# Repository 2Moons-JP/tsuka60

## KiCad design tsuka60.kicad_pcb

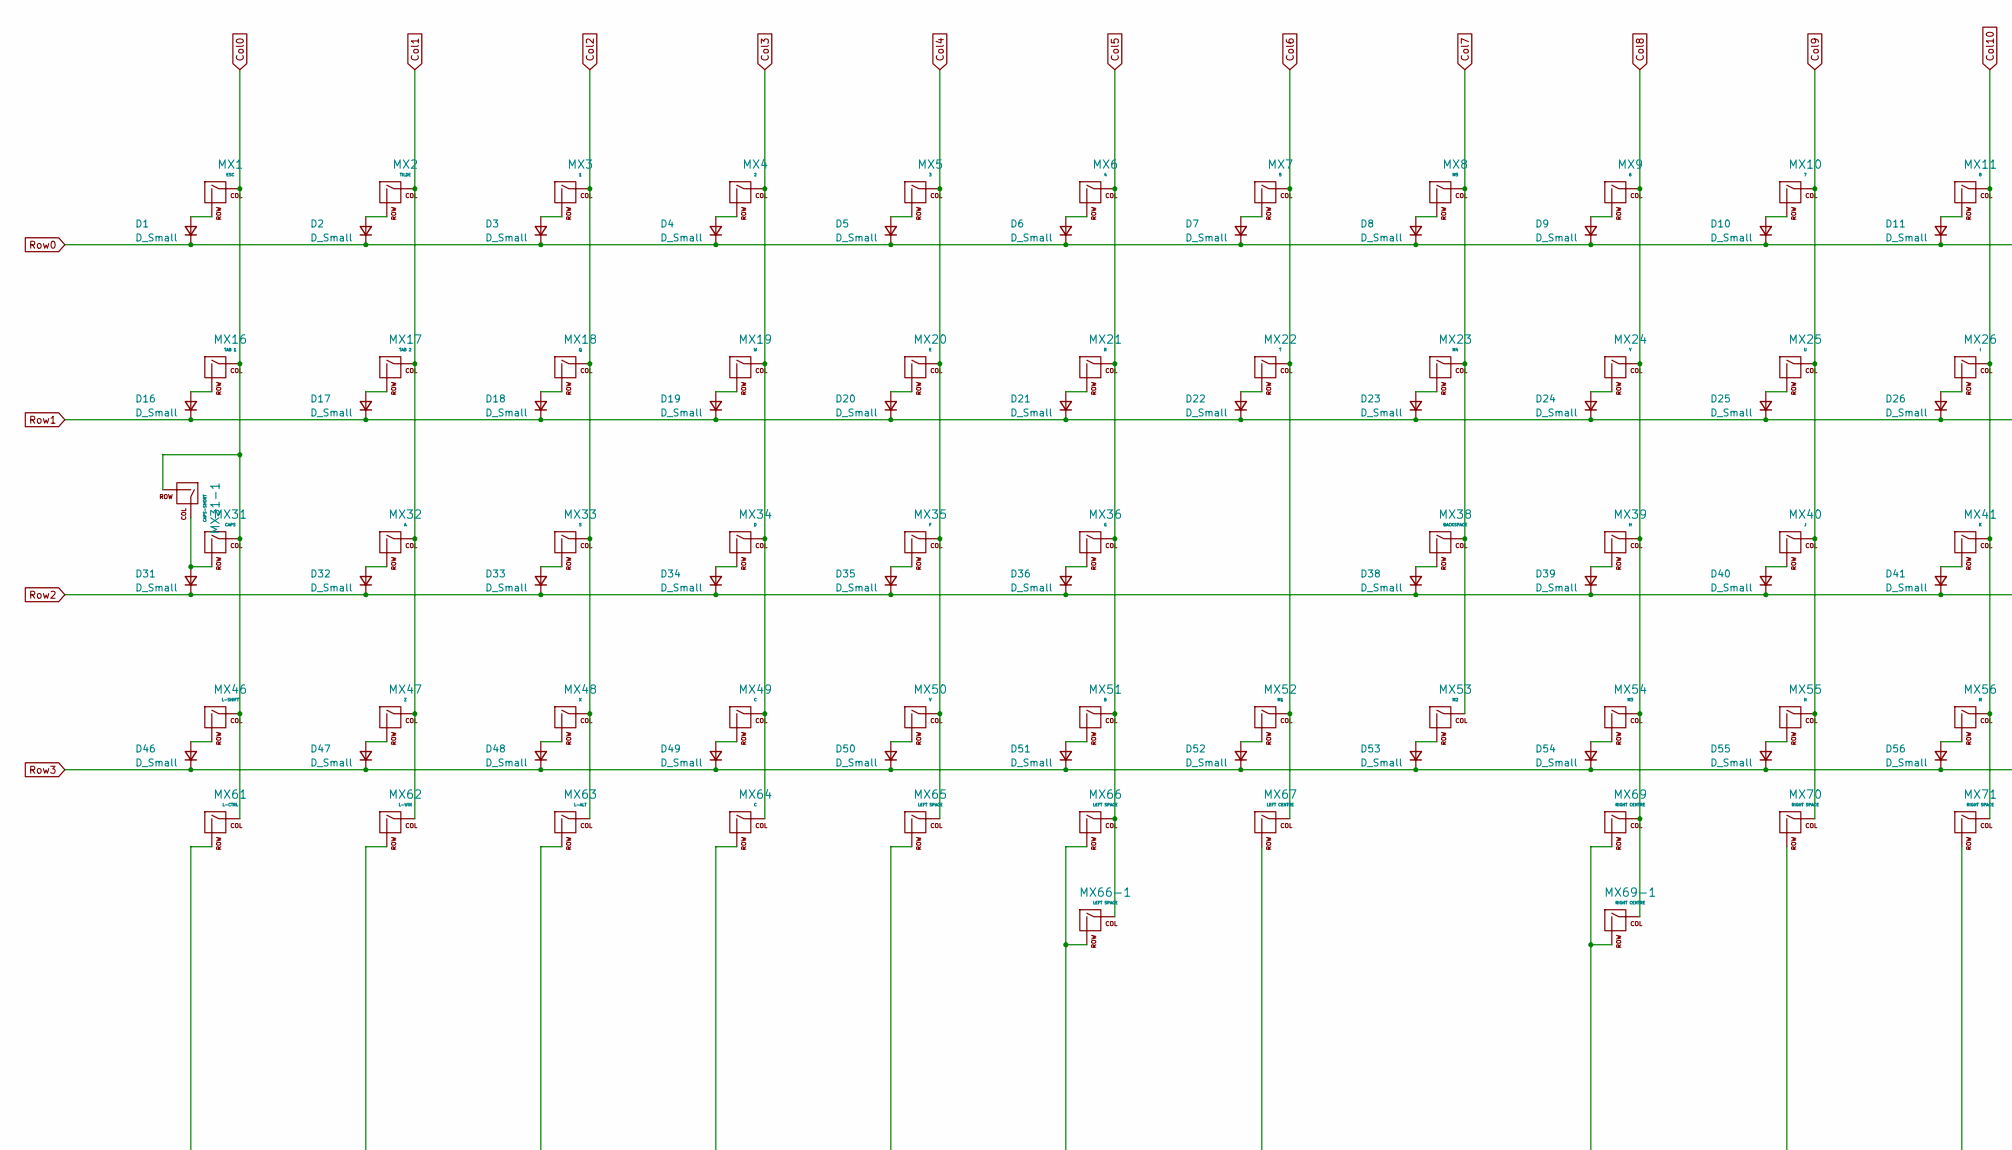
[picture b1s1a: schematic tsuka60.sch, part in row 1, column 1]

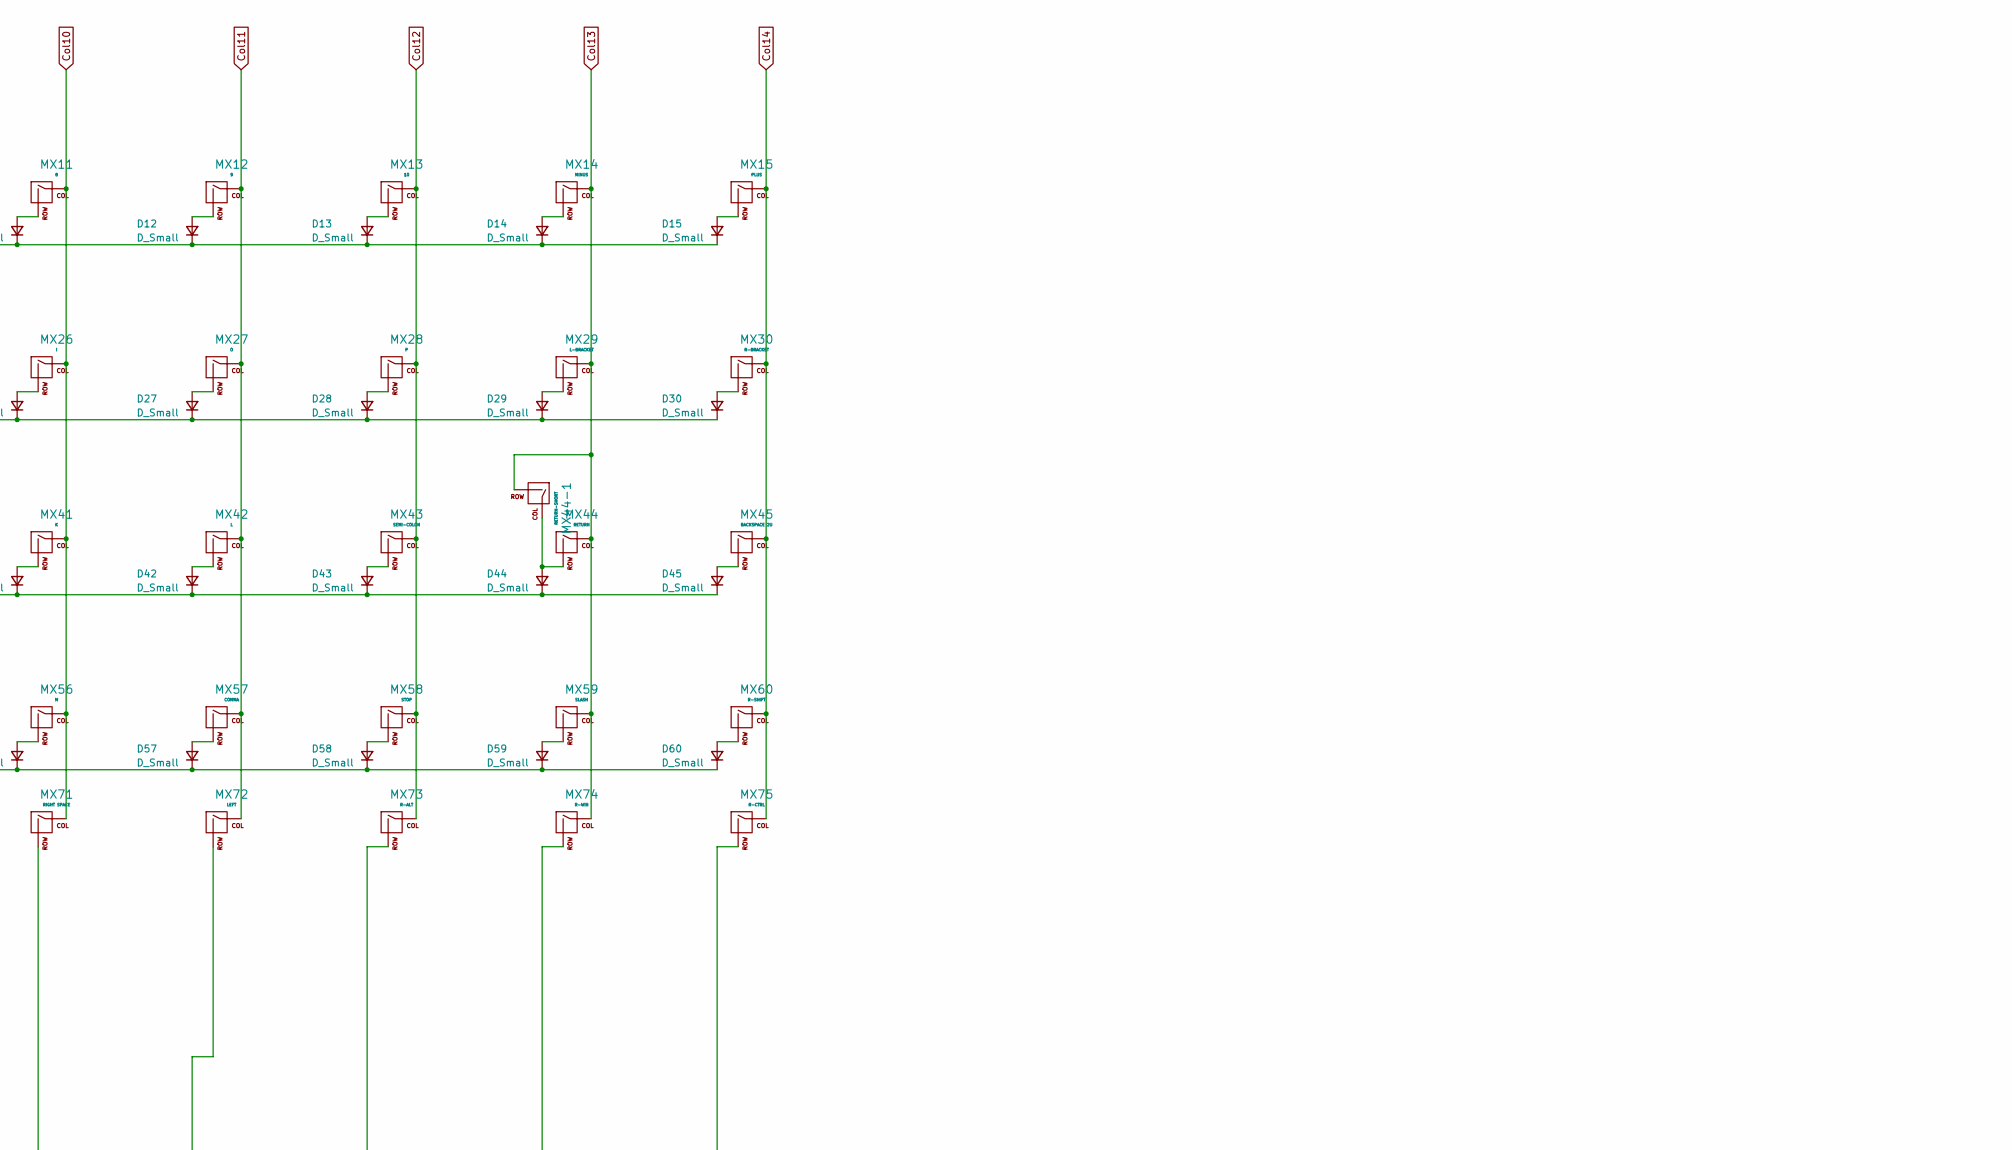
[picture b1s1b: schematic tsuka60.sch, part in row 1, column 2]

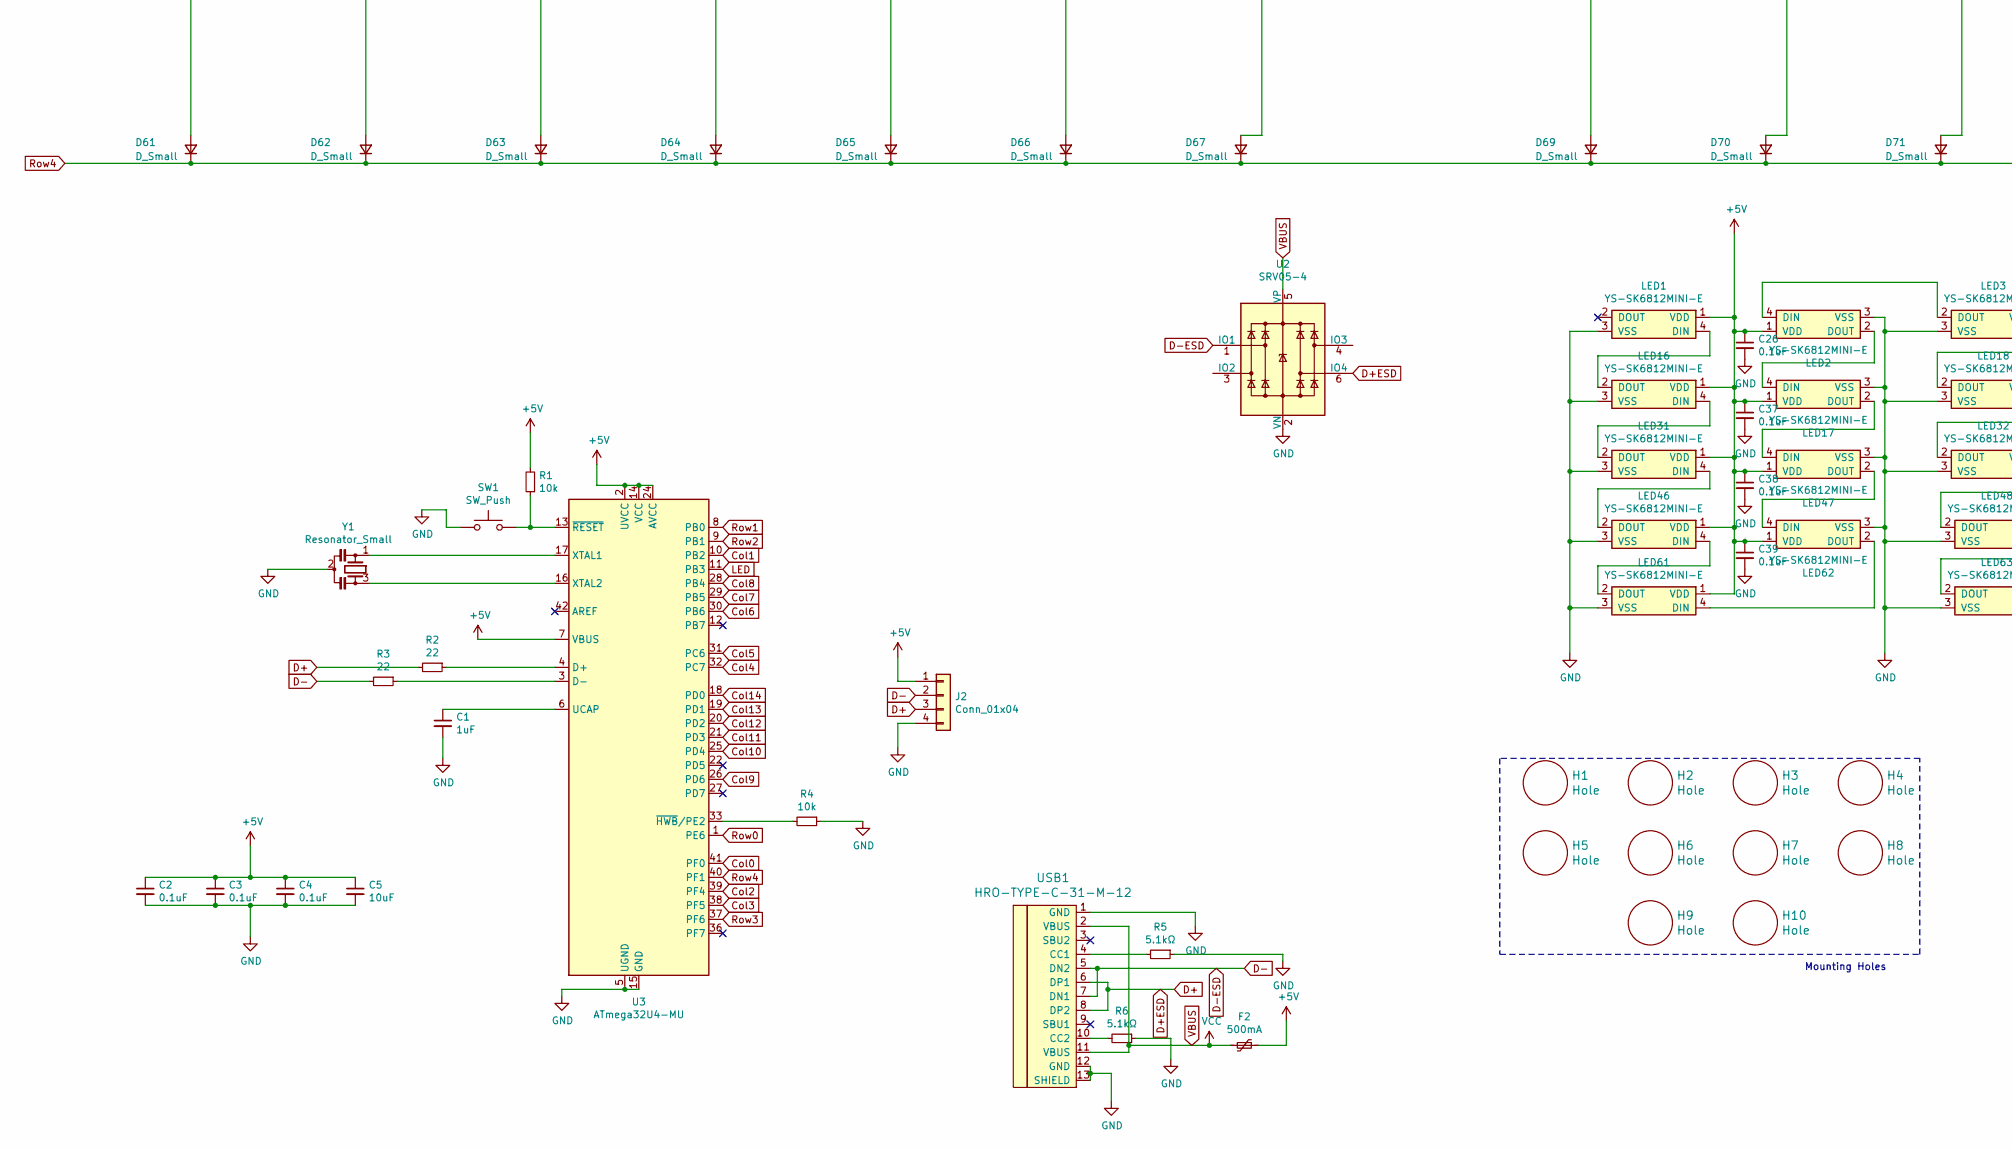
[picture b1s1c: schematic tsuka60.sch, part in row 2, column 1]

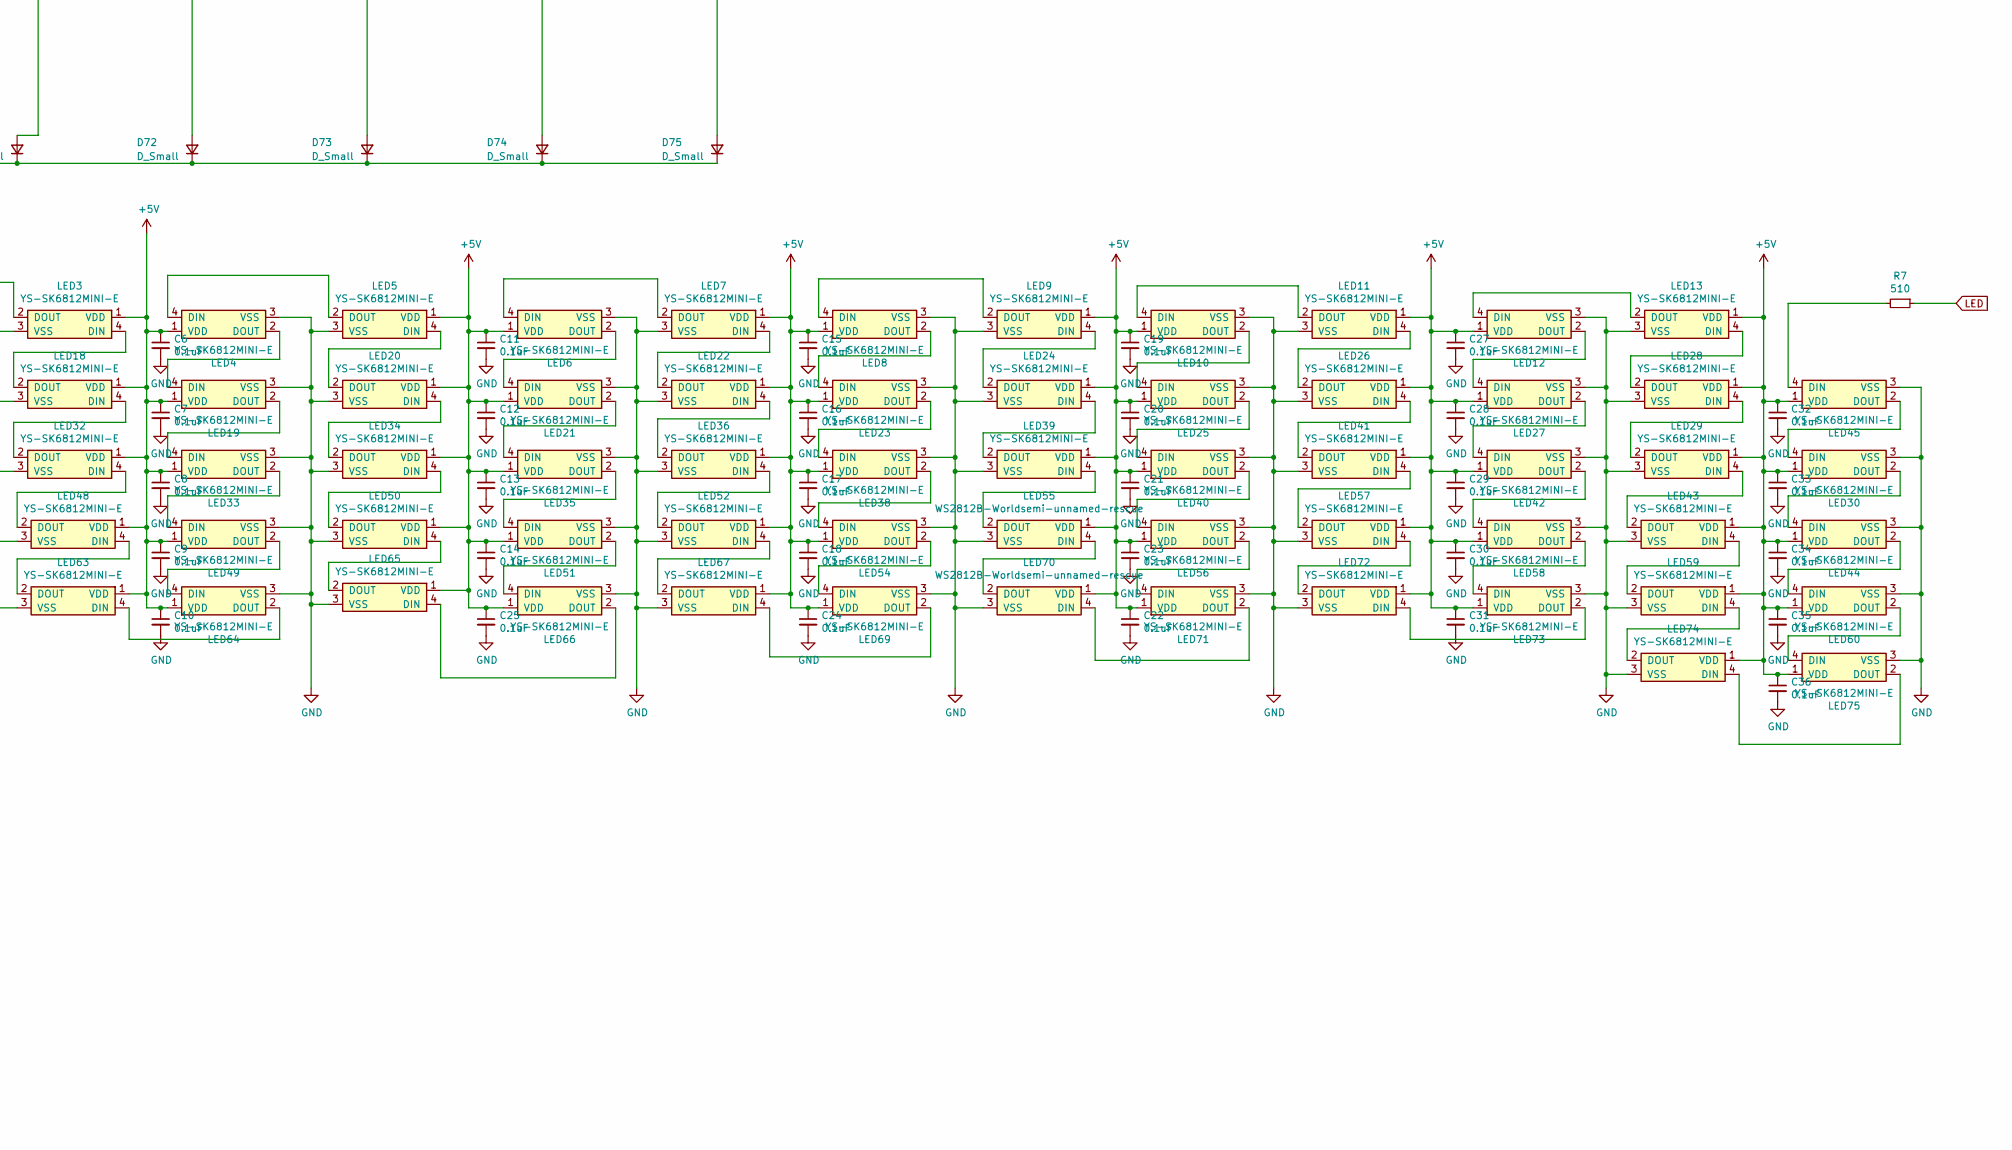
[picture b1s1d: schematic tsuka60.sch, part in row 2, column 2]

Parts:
C1: 1uF; C_0805_2012Metric
C2, C3, C4, C6, C7, C8, C9, C10, C11, C12, C13, C14, C15, C16, C17, C18, C19, C20, C21, C22, C23, C24, C25, C26, C27, C28, C29, C30, C31, C32, C33, C34, C35, C36, C37, C38, C39: 0.1uF; C_0805_2012Metric
C5: 10uF; C_0805_2012Metric
D1, D2, D3, D4, D5, D6, D7, D8, D9, D10, D11, D12, D13, D14, D15, D16, D17, D18, D19, D20, D21, D22, D23, D24, D25, D26, D27, D28, D29, D30, D31, D32, D33, D34, D35, D36, D38, D39, D40, D41, D42, D43, D44, D45, D46, D47, D48, D49, D50, D51, D52, D53, D54, D55, D56, D57, D58, D59, D60, D61, D62, D63, D64, D65, D66, D67, D69, D70, D71, D72, D73, D74, D75: D_Small; D_0805_2012Metric
F2: 500mA; Fuse_1206_3216Metric
H1, H10: Hole; halfSideHole
H2, H4, H5, H6, H8, H9: Hole; MoutingHole_Oval_7mm_5.0x2.5mm
H3: Hole; 2MoutingHole_Oval_7mm_5.0x2.5mm
H7: Hole; 3MoutingHole_Oval_7mm_5.0x2.5mm
J2: Conn_01x04; JST-SR-4
LED1, LED2, LED3, LED4, LED5, LED6, LED7, LED8, LED9, LED10, LED11, LED12, LED13, LED16, LED17, LED18, LED19, LED20, LED21, LED22, LED23, LED24, LED25, LED26, LED27, LED28, LED29, LED30, LED31, LED32, LED33, LED34, LED35, LED36, LED38, LED39, LED40, LED41, LED42, LED43, LED44, LED45, LED46, LED47, LED48, LED49, LED50, LED51, LED52, LED54, LED56, LED57, LED58, LED59, LED60, LED61, LED62, LED63, LED64, LED65, LED66, LED67, LED69, LED71, LED72, LED73, LED74, LED75: YS-SK6812MINI-E
LED55, LED70: WS2812B-Worldsemi-unnamed-rescue; YS-SK6812MINI-E
MX1: ESC; MX-1U-NoLED
MX2: TILDE; MX-1U-NoLED
MX3: 1; MX-1U-NoLED
MX4: 2; MX-1U-NoLED
MX5: 3; MX-1U-NoLED
MX6: 4; MX-1U-NoLED
MX7: 5; MX-1U-NoLED
MX8: M5; MX-1U-NoLED
MX9: 6; MX-1U-NoLED
MX10: 7; MX-1U-NoLED
MX11: 8; MX-1U-NoLED
MX12: 9; MX-1U-NoLED
MX13: 10; MX-1U-NoLED
MX14: MINUS; MX-1U-NoLED
MX15: PLUS; MX-1U-NoLED
MX16: TAB 1; MX-1U-NoLED
MX17: TAB 2; MX-1U-NoLED
MX18: Q; MX-1U-NoLED
MX19: W; MX-1U-NoLED
MX20: E; MX-1U-NoLED
MX21: R; MX-1U-NoLED
MX22: T; MX-1U-NoLED
MX23: M4; MX-1U-NoLED
MX24: Y; MX-1U-NoLED
MX25: U; MX-1U-NoLED
MX26: I; MX-1U-NoLED
MX27: O; MX-1U-NoLED
MX28: P; MX-1U-NoLED
MX29: L-BRACKET; MX-1U-NoLED
MX30: R-BRACKET; MX-1U-NoLED
MX31: CAPS; MX-1.75U-NoLED
MX31-1: CAPS-SHORT; MX-1.25U-NoLED
MX32: A; MX-1U-NoLED
MX33: S; MX-1U-NoLED
MX34: D; MX-1U-NoLED
MX35: F; MX-1U-NoLED
MX36: G; MX-1U-NoLED
MX38: BACKSPACE; MX-1.5U-NoLED
MX39: H; MX-1U-NoLED
MX40: J; MX-1U-NoLED
MX41: K; MX-1U-NoLED
MX42: L; MX-1U-NoLED
MX43: SEMI-COLON; MX-1U-NoLED
MX44: RETURN; MX-1.75U-NoLED
MX44-1: RETURN-SHORT; MX-1.25U-NoLED
MX45: BACKSPACE 2U; MX-2U-ReversedStabilizers-NoLED
MX46: L-SHIFT; MX-1.5U-NoLED
MX47: Z; MX-1U-NoLED
MX48: X; MX-1U-NoLED
MX49, MX64: C; MX-1U-NoLED
MX50: V; MX-1U-NoLED
MX51: B; MX-1U-NoLED
MX52: M1; MX-1U-NoLED
MX53: M2; MX-2U-NoLED
MX54: M3; MX-1U-NoLED
MX55: N; MX-1U-NoLED
MX56: M; MX-1U-NoLED
MX57: COMMA; MX-1U-NoLED
MX58: STOP; MX-1U-NoLED
MX59: SLASH; MX-1U-NoLED
MX60: R-SHIFT; MX-1.5U-NoLED
MX61: L-CTRL; MX-1.5U-NoLED
MX62: L-WIN; MX-1U-NoLED
MX63: L-ALT; MX-1U-NoLED
MX65, MX66: LEFT SPACE; MX-1U-NoLED
MX66-1: LEFT SPACE; MX-2U-NoLED
MX67: LEFT CENTRE; MX-1U-NoLED
MX69: RIGHT CENTRE; MX-1U-NoLED
MX69-1: RIGHT CENTRE; MX-2U-NoLED
MX70, MX71: RIGHT SPACE; MX-1U-NoLED
MX72: LEFT; MX-1U-NoLED
MX73: R-ALT; MX-1U-NoLED
MX74: R-WIN; MX-1U-NoLED
MX75: R-CTRL; MX-1.5U-NoLED
R1, R4: 10k; R_0805_2012Metric
R2, R3: 22; R_0805_2012Metric
R5, R6: 5.1kΩ; R_0805_2012Metric
R7: 510; R_0805_2012Metric
SW1: SW_Push; SKQG-1155865
U2: SRV05-4; SOT-23-6
U3: ATmega32U4-MU; QFN-44-1EP_7x7mm_P0.5mm_EP5.2x5.2mm
USB1: HRO-TYPE-C-31-M-12; HRO-TYPE-C-31-M-12-HandSoldering
Y1: Resonator_Small; Resonator_SMD_muRata_CSTxExxV-3Pin_3.0x1.1mm

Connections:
+5V: C2.1, C3.1, C4.1, C5.1, C6.1, C7.1, C8.1, C9.1, C10.1, C11.1, C12.1, C13.1, C14.1, C15.1, C16.1, C17.1, C18.1, C19.1, C20.1, C21.1, C22.1, C23.1, C24.1, C25.1, C26.1, C27.1, C28.1, C29.1, C30.1, C31.1, C32.1, C33.1, C34.1, C35.1, C36.1, C37.1, C38.1, C39.1, F2.1, J2.1, LED1.1 (VDD), LED2.1 (VDD), LED3.1 (VDD), LED4.1 (VDD), LED5.1 (VDD), LED6.1 (VDD), LED7.1 (VDD), LED8.1 (VDD), LED9.1 (VDD), LED10.1 (VDD), LED11.1 (VDD), LED12.1 (VDD), LED13.1 (VDD), LED16.1 (VDD), LED17.1 (VDD), LED18.1 (VDD), LED19.1 (VDD), LED20.1 (VDD), LED21.1 (VDD), LED22.1 (VDD), LED23.1 (VDD), LED24.1 (VDD), LED25.1 (VDD), LED26.1 (VDD), LED27.1 (VDD), LED28.1 (VDD), LED29.1 (VDD), LED30.1 (VDD), LED31.1 (VDD), LED32.1 (VDD), LED33.1 (VDD), LED34.1 (VDD), LED35.1 (VDD), LED36.1 (VDD), LED38.1 (VDD), LED39.1 (VDD), LED40.1 (VDD), LED41.1 (VDD), LED42.1 (VDD), LED43.1 (VDD), LED44.1 (VDD), LED45.1 (VDD), LED46.1 (VDD), LED47.1 (VDD), LED48.1 (VDD), LED49.1 (VDD), LED50.1 (VDD), LED51.1 (VDD), LED52.1 (VDD), LED54.1 (VDD), LED55.1 (VDD), LED56.1 (VDD), LED57.1 (VDD), LED58.1 (VDD), LED59.1 (VDD), LED60.1 (VDD), LED61.1 (VDD), LED62.1 (VDD), LED63.1 (VDD), LED64.1 (VDD), LED65.1 (VDD), LED66.1 (VDD), LED67.1 (VDD), LED69.1 (VDD), LED70.1 (VDD), LED71.1 (VDD), LED72.1 (VDD), LED73.1 (VDD), LED74.1 (VDD), LED75.1 (VDD), R1.2, U3.2 (UVCC), U3.7 (VBUS), U3.14 (VCC), U3.24 (AVCC), U3.34 (VCC), U3.44 (AVCC)
Col0: MX1.1 (COL), MX16.1 (COL), MX31.1 (COL), MX31-1.2 (ROW), MX46.1 (COL), MX61.1 (COL), U3.41 (PF0)
Col1: MX2.1 (COL), MX17.1 (COL), MX32.1 (COL), MX47.1 (COL), MX62.1 (COL), U3.10 (PB2)
Col2: MX3.1 (COL), MX18.1 (COL), MX33.1 (COL), MX48.1 (COL), MX63.1 (COL), U3.39 (PF4)
Col3: MX4.1 (COL), MX19.1 (COL), MX34.1 (COL), MX49.1 (COL), MX64.1 (COL), U3.38 (PF5)
Col4: MX5.1 (COL), MX20.1 (COL), MX35.1 (COL), MX50.1 (COL), MX65.1 (COL), U3.32 (PC7)
Col5: MX6.1 (COL), MX21.1 (COL), MX36.1 (COL), MX51.1 (COL), MX66.1 (COL), MX66-1.1 (COL), U3.31 (PC6)
Col6: MX7.1 (COL), MX22.1 (COL), MX52.1 (COL), MX67.1 (COL), U3.30 (PB6)
Col7: MX8.1 (COL), MX23.1 (COL), MX38.1 (COL), MX53.1 (COL), U3.29 (PB5)
Col8: MX9.1 (COL), MX24.1 (COL), MX39.1 (COL), MX54.1 (COL), MX69.1 (COL), MX69-1.1 (COL), U3.28 (PB4)
Col9: MX10.1 (COL), MX25.1 (COL), MX40.1 (COL), MX55.1 (COL), MX70.1 (COL), U3.26 (PD6)
Col10: MX11.1 (COL), MX26.1 (COL), MX41.1 (COL), MX56.1 (COL), MX71.1 (COL), U3.25 (PD4)
Col11: MX12.1 (COL), MX27.1 (COL), MX42.1 (COL), MX57.1 (COL), MX72.1 (COL), U3.21 (PD3)
Col12: MX13.1 (COL), MX28.1 (COL), MX43.1 (COL), MX58.1 (COL), MX73.1 (COL), U3.20 (PD2)
Col13: MX14.1 (COL), MX29.1 (COL), MX44.1 (COL), MX44-1.2 (ROW), MX59.1 (COL), MX74.1 (COL), U3.19 (PD1)
Col14: MX15.1 (COL), MX30.1 (COL), MX45.1 (COL), MX60.1 (COL), MX75.1 (COL), U3.18 (PD0)
D+: J2.3, R2.2, U2.6 (IO4), USB1.6 (DP1), USB1.8 (DP2)
D-: J2.2, R3.2, U2.1 (IO1), USB1.5 (DN2), USB1.7 (DN1)
GND: C1.2, C2.2, C3.2, C4.2, C5.2, C6.2, C7.2, C8.2, C9.2, C10.2, C11.2, C12.2, C13.2, C14.2, C15.2, C16.2, C17.2, C18.2, C19.2, C20.2, C21.2, C22.2, C23.2, C24.2, C25.2, C26.2, C27.2, C28.2, C29.2, C30.2, C31.2, C32.2, C33.2, C34.2, C35.2, C36.2, C37.2, C38.2, C39.2, J2.4, LED1.3 (VSS), LED2.3 (VSS), LED3.3 (VSS), LED4.3 (VSS), LED5.3 (VSS), LED6.3 (VSS), LED7.3 (VSS), LED8.3 (VSS), LED9.3 (VSS), LED10.3 (VSS), LED11.3 (VSS), LED12.3 (VSS), LED13.3 (VSS), LED16.3 (VSS), LED17.3 (VSS), LED18.3 (VSS), LED19.3 (VSS), LED20.3 (VSS), LED21.3 (VSS), LED22.3 (VSS), LED23.3 (VSS), LED24.3 (VSS), LED25.3 (VSS), LED26.3 (VSS), LED27.3 (VSS), LED28.3 (VSS), LED29.3 (VSS), LED30.3 (VSS), LED31.3 (VSS), LED32.3 (VSS), LED33.3 (VSS), LED34.3 (VSS), LED35.3 (VSS), LED36.3 (VSS), LED38.3 (VSS), LED39.3 (VSS), LED40.3 (VSS), LED41.3 (VSS), LED42.3 (VSS), LED43.3 (VSS), LED44.3 (VSS), LED45.3 (VSS), LED46.3 (VSS), LED47.3 (VSS), LED48.3 (VSS), LED49.3 (VSS), LED50.3 (VSS), LED51.3 (VSS), LED52.3 (VSS), LED54.3 (VSS), LED55.3 (VSS), LED56.3 (VSS), LED57.3 (VSS), LED58.3 (VSS), LED59.3 (VSS), LED60.3 (VSS), LED61.3 (VSS), LED62.3 (VSS), LED63.3 (VSS), LED64.3 (VSS), LED65.3 (VSS), LED66.3 (VSS), LED67.3 (VSS), LED69.3 (VSS), LED70.3 (VSS), LED71.3 (VSS), LED72.3 (VSS), LED73.3 (VSS), LED74.3 (VSS), LED75.3 (VSS), R4.1, R5.1, R6.1, SW1.1, U2.2 (VN), U3.5 (UGND), U3.15 (GND), U3.23 (GND), U3.35 (GND), U3.43 (GND), U3.45 (GND), USB1.1 (GND), USB1.12 (GND), USB1.13 (SHIELD), Y1.2
LED: R7.1, U3.11 (PB3)
unnamed: C1.1, U3.6 (UCAP)
unnamed: D1.2 (A), MX1.2 (ROW)
unnamed: D2.2 (A), MX2.2 (ROW)
unnamed: D3.2 (A), MX3.2 (ROW)
unnamed: D4.2 (A), MX4.2 (ROW)
unnamed: D5.2 (A), MX5.2 (ROW)
unnamed: D6.2 (A), MX6.2 (ROW)
unnamed: D7.2 (A), MX7.2 (ROW)
unnamed: D8.2 (A), MX8.2 (ROW)
unnamed: D9.2 (A), MX9.2 (ROW)
unnamed: D10.2 (A), MX10.2 (ROW)
unnamed: D11.2 (A), MX11.2 (ROW)
unnamed: D12.2 (A), MX12.2 (ROW)
unnamed: D13.2 (A), MX13.2 (ROW)
unnamed: D14.2 (A), MX14.2 (ROW)
unnamed: D15.2 (A), MX15.2 (ROW)
unnamed: D16.2 (A), MX16.2 (ROW)
unnamed: D17.2 (A), MX17.2 (ROW)
unnamed: D18.2 (A), MX18.2 (ROW)
unnamed: D19.2 (A), MX19.2 (ROW)
unnamed: D20.2 (A), MX20.2 (ROW)
unnamed: D21.2 (A), MX21.2 (ROW)
unnamed: D22.2 (A), MX22.2 (ROW)
unnamed: D23.2 (A), MX23.2 (ROW)
unnamed: D24.2 (A), MX24.2 (ROW)
unnamed: D25.2 (A), MX25.2 (ROW)
unnamed: D26.2 (A), MX26.2 (ROW)
unnamed: D27.2 (A), MX27.2 (ROW)
unnamed: D28.2 (A), MX28.2 (ROW)
unnamed: D29.2 (A), MX29.2 (ROW)
unnamed: D30.2 (A), MX30.2 (ROW)
unnamed: D31.2 (A), MX31.2 (ROW), MX31-1.1 (COL)
unnamed: D32.2 (A), MX32.2 (ROW)
unnamed: D33.2 (A), MX33.2 (ROW)
unnamed: D34.2 (A), MX34.2 (ROW)
unnamed: D35.2 (A), MX35.2 (ROW)
unnamed: D36.2 (A), MX36.2 (ROW)
unnamed: D38.2 (A), MX38.2 (ROW)
unnamed: D39.2 (A), MX39.2 (ROW)
unnamed: D40.2 (A), MX40.2 (ROW)
unnamed: D41.2 (A), MX41.2 (ROW)
unnamed: D42.2 (A), MX42.2 (ROW)
unnamed: D43.2 (A), MX43.2 (ROW)
unnamed: D44.2 (A), MX44.2 (ROW), MX44-1.1 (COL)
unnamed: D45.2 (A), MX45.2 (ROW)
unnamed: D46.2 (A), MX46.2 (ROW)
unnamed: D47.2 (A), MX47.2 (ROW)
unnamed: D48.2 (A), MX48.2 (ROW)
unnamed: D49.2 (A), MX49.2 (ROW)
unnamed: D50.2 (A), MX50.2 (ROW)
unnamed: D51.2 (A), MX51.2 (ROW)
unnamed: D52.2 (A), MX52.2 (ROW)
unnamed: D53.2 (A), MX53.2 (ROW)
unnamed: D54.2 (A), MX54.2 (ROW)
unnamed: D55.2 (A), MX55.2 (ROW)
unnamed: D56.2 (A), MX56.2 (ROW)
unnamed: D57.2 (A), MX57.2 (ROW)
unnamed: D58.2 (A), MX58.2 (ROW)
unnamed: D59.2 (A), MX59.2 (ROW)
unnamed: D60.2 (A), MX60.2 (ROW)
unnamed: D61.2 (A), MX61.2 (ROW)
unnamed: D62.2 (A), MX62.2 (ROW)
unnamed: D63.2 (A), MX63.2 (ROW)
unnamed: D64.2 (A), MX64.2 (ROW)
unnamed: D65.2 (A), MX65.2 (ROW)
unnamed: D66.2 (A), MX66.2 (ROW), MX66-1.2 (ROW)
unnamed: D67.2 (A), MX67.2 (ROW)
unnamed: D69.2 (A), MX69.2 (ROW), MX69-1.2 (ROW)
unnamed: D70.2 (A), MX70.2 (ROW)
unnamed: D71.2 (A), MX71.2 (ROW)
unnamed: D72.2 (A), MX72.2 (ROW)
unnamed: D73.2 (A), MX73.2 (ROW)
unnamed: D74.2 (A), MX74.2 (ROW)
unnamed: D75.2 (A), MX75.2 (ROW)
unnamed: LED1.4 (DIN), LED16.2 (DOUT)
unnamed: LED2.4 (DIN), LED3.2 (DOUT)
unnamed: LED4.4 (DIN), LED5.2 (DOUT)
unnamed: LED6.4 (DIN), LED7.2 (DOUT)
unnamed: LED8.4 (DIN), LED9.2 (DOUT)
unnamed: LED10.2 (DOUT), LED25.4 (DIN)
unnamed: LED10.4 (DIN), LED11.2 (DOUT)
unnamed: LED11.4 (DIN), LED26.2 (DOUT)
unnamed: LED12.2 (DOUT), LED27.4 (DIN)
unnamed: LED12.4 (DIN), LED13.2 (DOUT)
unnamed: LED13.4 (DIN), LED28.2 (DOUT)
unnamed: LED16.4 (DIN), LED31.2 (DOUT)
unnamed: LED17.2 (DOUT), LED47.4 (DIN)
unnamed: LED2.2 (DOUT), LED17.4 (DIN)
unnamed: LED3.4 (DIN), LED18.2 (DOUT)
unnamed: LED18.4 (DIN), LED32.2 (DOUT)
unnamed: LED19.2 (DOUT), LED33.4 (DIN)
unnamed: LED4.2 (DOUT), LED19.4 (DIN)
unnamed: LED5.4 (DIN), LED20.2 (DOUT)
unnamed: LED20.4 (DIN), LED34.2 (DOUT)
unnamed: LED21.2 (DOUT), LED35.4 (DIN)
unnamed: LED6.2 (DOUT), LED21.4 (DIN)
unnamed: LED7.4 (DIN), LED22.2 (DOUT)
unnamed: LED22.4 (DIN), LED36.2 (DOUT)
unnamed: LED23.2 (DOUT), LED38.4 (DIN)
unnamed: LED8.2 (DOUT), LED23.4 (DIN)
unnamed: LED9.4 (DIN), LED24.2 (DOUT)
unnamed: LED24.4 (DIN), LED39.2 (DOUT)
unnamed: LED25.2 (DOUT), LED40.4 (DIN)
unnamed: LED26.4 (DIN), LED41.2 (DOUT)
unnamed: LED27.2 (DOUT), LED42.4 (DIN)
unnamed: LED28.4 (DIN), LED29.2 (DOUT)
unnamed: LED29.4 (DIN), LED43.2 (DOUT)
unnamed: LED30.2 (DOUT), LED44.4 (DIN)
unnamed: LED30.4 (DIN), LED45.2 (DOUT)
unnamed: LED31.4 (DIN), LED46.2 (DOUT)
unnamed: LED32.4 (DIN), LED48.2 (DOUT)
unnamed: LED33.2 (DOUT), LED49.4 (DIN)
unnamed: LED34.4 (DIN), LED50.2 (DOUT)
unnamed: LED35.2 (DOUT), LED51.4 (DIN)
unnamed: LED36.4 (DIN), LED52.2 (DOUT)
unnamed: LED38.2 (DOUT), LED54.4 (DIN)
unnamed: LED39.4 (DIN), LED55.2 (DOUT)
unnamed: LED40.2 (DOUT), LED56.4 (DIN)
unnamed: LED41.4 (DIN), LED57.2 (DOUT)
unnamed: LED42.2 (DOUT), LED58.4 (DIN)
unnamed: LED43.4 (DIN), LED59.2 (DOUT)
unnamed: LED44.2 (DOUT), LED60.4 (DIN)
unnamed: LED45.4 (DIN), R7.2
unnamed: LED46.4 (DIN), LED61.2 (DOUT)
unnamed: LED47.2 (DOUT), LED62.4 (DIN)
unnamed: LED48.4 (DIN), LED63.2 (DOUT)
unnamed: LED49.2 (DOUT), LED64.4 (DIN)
unnamed: LED50.4 (DIN), LED65.2 (DOUT)
unnamed: LED51.2 (DOUT), LED66.4 (DIN)
unnamed: LED52.4 (DIN), LED67.2 (DOUT)
unnamed: LED54.2 (DOUT), LED69.4 (DIN)
unnamed: LED55.4 (DIN), LED70.2 (DOUT)
unnamed: LED56.2 (DOUT), LED71.4 (DIN)
unnamed: LED57.4 (DIN), LED72.2 (DOUT)
unnamed: LED58.2 (DOUT), LED73.4 (DIN)
unnamed: LED59.4 (DIN), LED74.2 (DOUT)
unnamed: LED60.2 (DOUT), LED75.4 (DIN)
unnamed: LED61.4 (DIN), LED62.2 (DOUT)
unnamed: LED63.4 (DIN), LED64.2 (DOUT)
unnamed: LED65.4 (DIN), LED66.2 (DOUT)
unnamed: LED67.4 (DIN), LED69.2 (DOUT)
unnamed: LED70.4 (DIN), LED71.2 (DOUT)
unnamed: LED72.4 (DIN), LED73.2 (DOUT)
unnamed: LED74.4 (DIN), LED75.2 (DOUT)
unnamed: R1.1, SW1.2, U3.13 (~RESET)
unnamed: R2.1, U3.4 (D+)
unnamed: R3.1, U3.3 (D-)
unnamed: R4.2, U3.33 (~HWB~/PE2)
unnamed: R5.2, USB1.4 (CC1)
unnamed: R6.2, USB1.10 (CC2)
unnamed: U3.16 (XTAL2), Y1.3
unnamed: U3.17 (XTAL1), Y1.1
Row0: D1.1 (K), D2.1 (K), D3.1 (K), D4.1 (K), D5.1 (K), D6.1 (K), D7.1 (K), D8.1 (K), D9.1 (K), D10.1 (K), D11.1 (K), D12.1 (K), D13.1 (K), D14.1 (K), D15.1 (K), U3.1 (PE6)
Row1: D16.1 (K), D17.1 (K), D18.1 (K), D19.1 (K), D20.1 (K), D21.1 (K), D22.1 (K), D23.1 (K), D24.1 (K), D25.1 (K), D26.1 (K), D27.1 (K), D28.1 (K), D29.1 (K), D30.1 (K), U3.8 (PB0)
Row2: D31.1 (K), D32.1 (K), D33.1 (K), D34.1 (K), D35.1 (K), D36.1 (K), D38.1 (K), D39.1 (K), D40.1 (K), D41.1 (K), D42.1 (K), D43.1 (K), D44.1 (K), D45.1 (K), U3.9 (PB1)
Row3: D46.1 (K), D47.1 (K), D48.1 (K), D49.1 (K), D50.1 (K), D51.1 (K), D52.1 (K), D53.1 (K), D54.1 (K), D55.1 (K), D56.1 (K), D57.1 (K), D58.1 (K), D59.1 (K), D60.1 (K), U3.37 (PF6)
Row4: D61.1 (K), D62.1 (K), D63.1 (K), D64.1 (K), D65.1 (K), D66.1 (K), D67.1 (K), D69.1 (K), D70.1 (K), D71.1 (K), D72.1 (K), D73.1 (K), D74.1 (K), D75.1 (K), U3.40 (PF1)
VBUS: F2.2, U2.5 (VP), USB1.2 (VBUS), USB1.11 (VBUS)

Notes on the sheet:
Mounting Holes

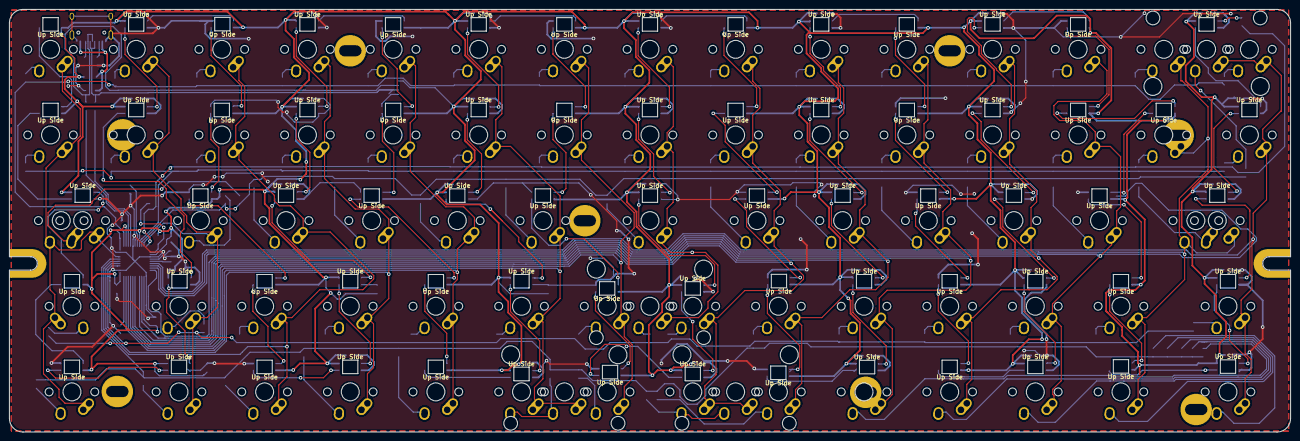
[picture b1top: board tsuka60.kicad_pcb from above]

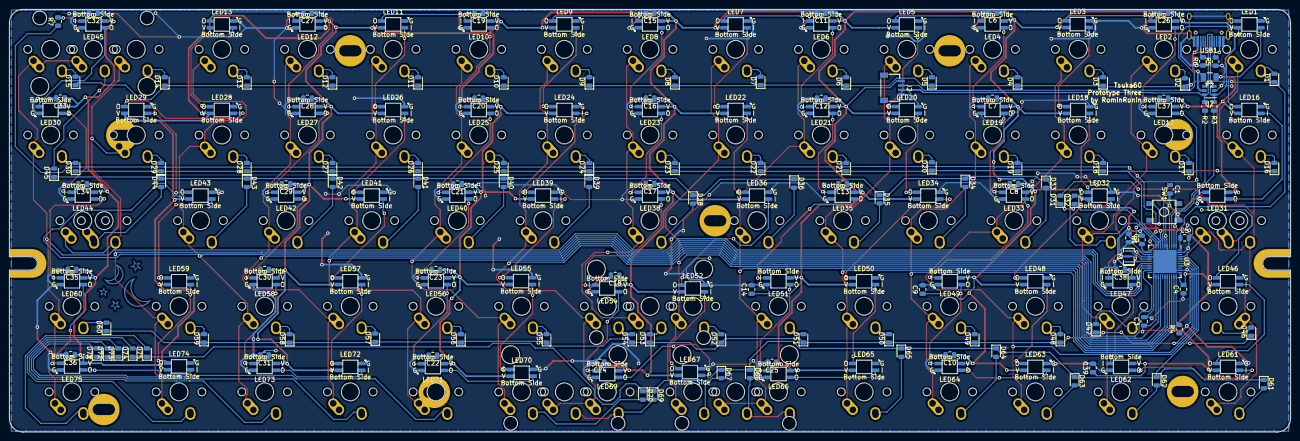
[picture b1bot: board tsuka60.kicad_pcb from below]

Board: 2 copper layers, 285.0 x 94.0 mm, 283 parts (197 on the bottom side), 178 nets.

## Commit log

2021-02-19 2/19
2021-03-01 3/1/2021
2021-03-05 3/5/2021
2021-03-16 3/16/2021
